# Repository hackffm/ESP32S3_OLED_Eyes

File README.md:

# ESP32S3_OLED_Eyes
Touch-sensitive OLED Eyes for ESP32-S3 modules based on playfultechnology / esp32-eyes. A badge from Hackerspace-FFM.de that shows eye animation and name on the OLED display.

This is a picture of the badge: 

More info in [Hackerspace-FFM Wiki](https://www.hackerspace-ffm.de/wiki/index.php?title=Hackerspace-FFM_Badge)

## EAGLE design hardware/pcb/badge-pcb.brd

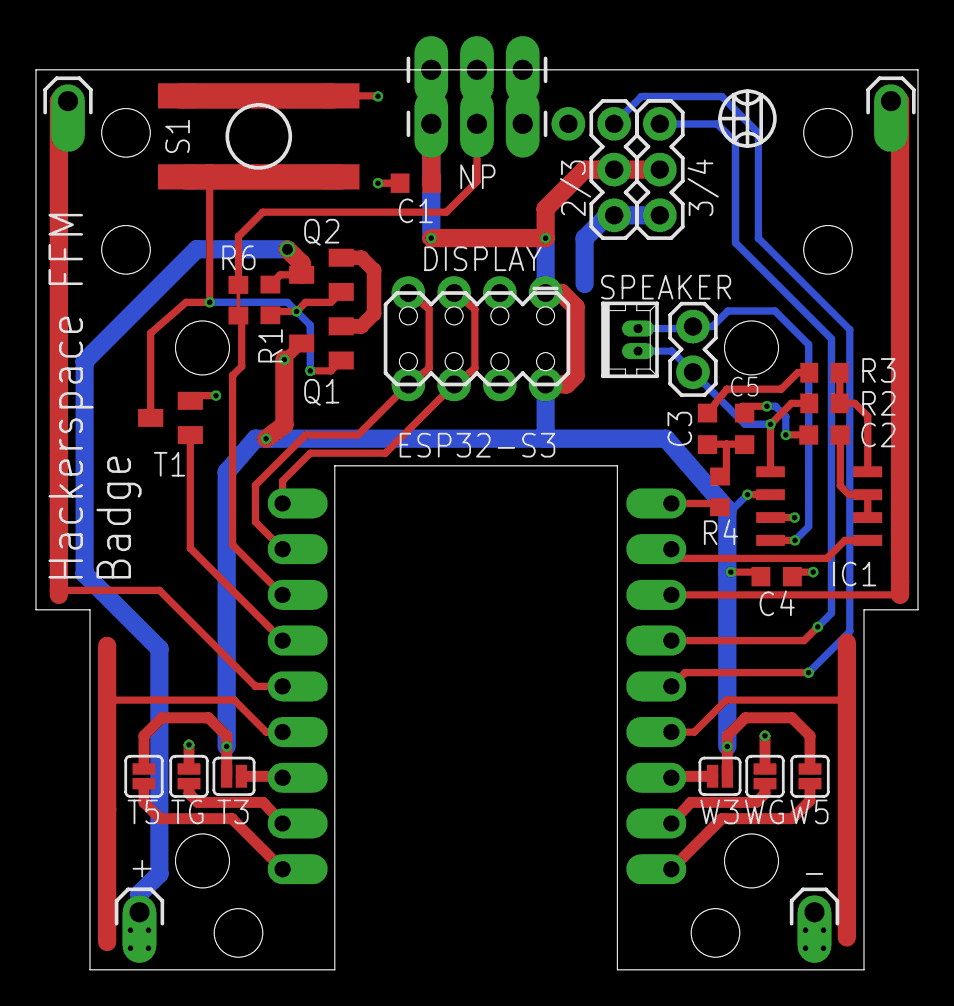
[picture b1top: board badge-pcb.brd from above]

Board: 2 copper layers, 49.0 x 50.0 mm, 34 parts (0 on the bottom side), 28 nets.

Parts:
2/3, 3/4: 455-1750-1-ND; 1X03
+: M01OFFSET; 1X01_OFFSET
-: M01OFFSET; 1X01_OFFSET
C1, C2, C3, C4: 1µF; C0603K
C5: 1nF; C0603K
DISPLAY: 2X04DRILL; 2X4-DRILL
ESP32-S3: ESP32-S3-MINI
IC1: LM4861M; SOIC8
J1: 1X02
J3: 455-1750-1-ND; 1X03_LONGPADS
JP9, JP11: M01OFFSET; 1X01_OFFSET
JP10: M01PTH; M01_1X01
NP: 455-1750-1-ND; 1X03_LONGPADS
Q1, Q2: AO3415A; SOT23-3PIN
R1, R2, R3: 22K; R0603
R4: 1K; R0603
R6: 470R; R0603
S1: JTP-1138EM
SPEAKER: 53047-02
T1: MMUN2213LT1G; SOT23
T3, T5: JUMPER-SMT_2_NO_SILK; SMT-JUMPER_2_NO_SILK
TG: JUMPER-SMT_2_NO_SILK; SMT-JUMPER_2_NO_SILK
W3, W5: JUMPER-SMT_2_NO_SILK; SMT-JUMPER_2_NO_SILK
WG: JUMPER-SMT_2_NO_SILK; SMT-JUMPER_2_NO_SILK

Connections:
2/3: 2/3.3, ESP32-S3.2
3/4: 3/4.3, ESP32-S3.3
AUDIO: ESP32-S3.6, R4.2
B: ESP32-S3.4, JP9.1
D: ESP32-S3.11, JP11.1
GND: 2/3.1, 3/4.1, -.1, C1.2, C2.2, C4.2, C5.2, DISPLAY.3A, DISPLAY.4A, IC1.7, J3.1, JP10.1, NP.1, S1.3, S1.4, T1.2, TG.1, WG.1
unnamed: ESP32-S3.3V3, W3.2
unnamed: ESP32-S3.13, T3.2
unnamed: ESP32-S3.RX, TG.2
unnamed: ESP32-S3.GND, WG.2
unnamed: Q1.2, Q2.2
unnamed: ESP32-S3.5V, W5.2
unnamed: +.1, Q2.3, R1.2
unnamed: Q1.1, Q2.1, R1.1, S1.1, S1.2, T1.3
unnamed: IC1.8, J1.2, SPEAKER.2
unnamed: ESP32-S3.TX, T5.1
unnamed: IC1.5, J1.1, R2.2, SPEAKER.1
unnamed: IC1.4, R2.1, R3.2
unnamed: C2.1, IC1.2, IC1.3
unnamed: C3.2, R3.1
unnamed: C3.1, C5.1, R4.1
unnamed: J3.2, NP.2, R6.2
NP: ESP32-S3.9, R6.1
PWR: ESP32-S3.10, T1.1
SCK: DISPLAY.5A, DISPLAY.6A, ESP32-S3.7
SDA: DISPLAY.7A, DISPLAY.8A, ESP32-S3.8
SHUTDOWN: ESP32-S3.5, IC1.1
VCC: 2/3.2, 3/4.2, C1.1, C4.1, DISPLAY.1A, DISPLAY.2A, IC1.6, J3.3, NP.3, Q1.3, T3.1, T5.2, W3.1, W5.1

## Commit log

2025-02-24 Add touch control
2025-02-24 Boot toggles emos
2025-03-09 Audiotests
2025-03-24 Big cleanup #1
2025-03-26 cleanup2
2025-03-26 Clean 3
2025-03-27 Ani-Cycle
2025-03-28 Add customizable Badge name
2025-03-28 Web OTA
2025-03-28 start sound changed
2025-03-28 some face
2025-03-28 in terminal naming mode switch to screen mode name
2025-03-30 minor stuff
2025-04-04 Touch to lib
2025-04-09 Post build creates pull-FW
2025-04-20 More clean-up, Badge should be able to open/close doors in Hackerspace via EspNow.
2025-05-05 Changed to pioarduino
2025-05-09 Updates for door access
2025-06-20 Big cleanup
2025-06-24 Add: comments in README.md
2025-10-05 drawCenteredUTF8Text added, formats Badge Name nicely big fully automatic.
2025-10-06 FW Update possible by holding button when no display and blinking red/blue.
2025-10-08 Radar started, badges now Tx its name.
2025-10-09 A little docu.

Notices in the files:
parts and their libraries:
SparkFun-Jumpers: Licensing: Creative Commons ShareAlike 4.0 International - https://creativecommons.org/licenses/by-sa/4.0
